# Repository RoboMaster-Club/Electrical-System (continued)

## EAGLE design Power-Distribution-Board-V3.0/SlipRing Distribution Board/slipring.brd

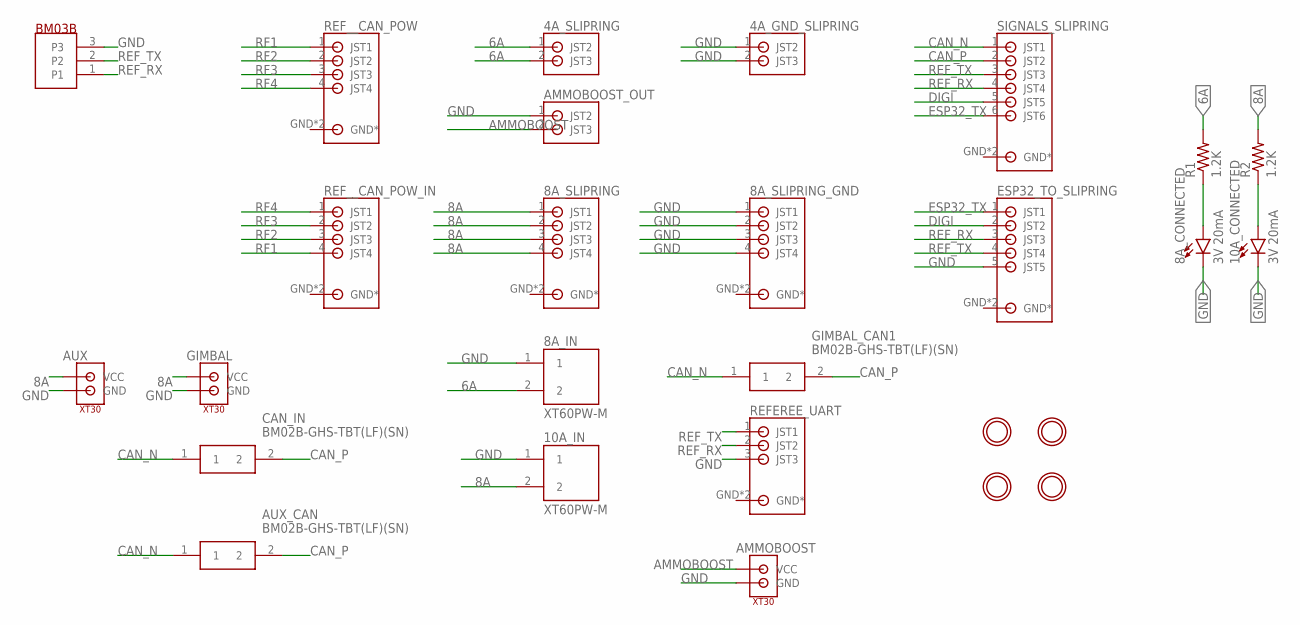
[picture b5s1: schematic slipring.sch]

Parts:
4A_GND_SLIPRING, 4A_SLIPRING: S2B-PH-SM4_TB
8A_CONNECTED, 10A_CONNECTED: 3V 20mA; LED-1206
8A_IN, 10A_IN: XT60PW-M; AMASS_XT60PW-M
8A_SLIPRING, 8A_SLIPRING_GND: S4B-PH-SM4_TB
AMMOBOOST: XT30
AMMOBOOST_OUT: S2B-PH-SM4_TB
AUX: XT30
AUX_CAN: BM02B-GHS-TBT(LF)(SN); BM02B-GHS-TBT_1
CAN_IN: BM02B-GHS-TBT(LF)(SN); BM02B-GHS-TBT_1
ESP32_TO_SLIPRING: S5B-PH-SM4_TB
GIMBAL: XT30
GIMBAL_CAN1: BM02B-GHS-TBT(LF)(SN); BM02B-GHS-TBT_1
R1, R2: 1.2K; R2010
REFEREE_UART: S3B-PH-SM4_TB
REF_UART: BM03-GHS_TBT; BM03-GHS-TBT
REF__CAN_POW: S4B-PH-SM4_TB
REF__CAN_POW_IN: S4B-PH-SM4_TB
SIGNALS_SLIPRING: S6B-PH-SM4_TB
U$1, U$2, U$4, U$49: MOUNTINGHOLE2.5; MOUNTINGHOLE_2.5_PLATED

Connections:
6A: 4A_SLIPRING.1 (JST2), 4A_SLIPRING.2 (JST3), 8A_IN.2, R1.2
8A: 8A_SLIPRING.1 (JST1), 8A_SLIPRING.2 (JST2), 8A_SLIPRING.3 (JST3), 8A_SLIPRING.4 (JST4), 10A_IN.2, AUX.P$2 (VCC), GIMBAL.P$2 (VCC), R2.2
AMMOBOOST: AMMOBOOST.P$2 (VCC), AMMOBOOST_OUT.2 (JST3)
CAN_N: AUX_CAN.1, CAN_IN.1, GIMBAL_CAN1.1, SIGNALS_SLIPRING.1 (JST1)
CAN_P: AUX_CAN.2, CAN_IN.2, GIMBAL_CAN1.2, SIGNALS_SLIPRING.2 (JST2)
DIGI: ESP32_TO_SLIPRING.2 (JST2), SIGNALS_SLIPRING.5 (JST5)
ESP32_TX: ESP32_TO_SLIPRING.1 (JST1), SIGNALS_SLIPRING.6 (JST6)
GND: 4A_GND_SLIPRING.1 (JST2), 4A_GND_SLIPRING.2 (JST3), 8A_CONNECTED.C, 8A_IN.1, 8A_SLIPRING_GND.1 (JST1), 8A_SLIPRING_GND.2 (JST2), 8A_SLIPRING_GND.3 (JST3), 8A_SLIPRING_GND.4 (JST4), 10A_CONNECTED.C, 10A_IN.1, AMMOBOOST.P$1 (GND), AMMOBOOST_OUT.1 (JST2), AUX.P$1 (GND), ESP32_TO_SLIPRING.5 (JST5), GIMBAL.P$1 (GND), REFEREE_UART.3 (JST3), REF_UART.3
unnamed: 10A_CONNECTED.A, R2.1
unnamed: 8A_CONNECTED.A, R1.1
REF_RX: ESP32_TO_SLIPRING.3 (JST3), REFEREE_UART.2 (JST2), REF_UART.1, SIGNALS_SLIPRING.4 (JST4)
REF_TX: ESP32_TO_SLIPRING.4 (JST4), REFEREE_UART.1 (JST1), REF_UART.2, SIGNALS_SLIPRING.3 (JST3)
RF1: REF__CAN_POW.1 (JST1), REF__CAN_POW_IN.4 (JST4)
RF2: REF__CAN_POW.2 (JST2), REF__CAN_POW_IN.3 (JST3)
RF3: REF__CAN_POW.3 (JST3), REF__CAN_POW_IN.2 (JST2)
RF4: REF__CAN_POW.4 (JST4), REF__CAN_POW_IN.1 (JST1)

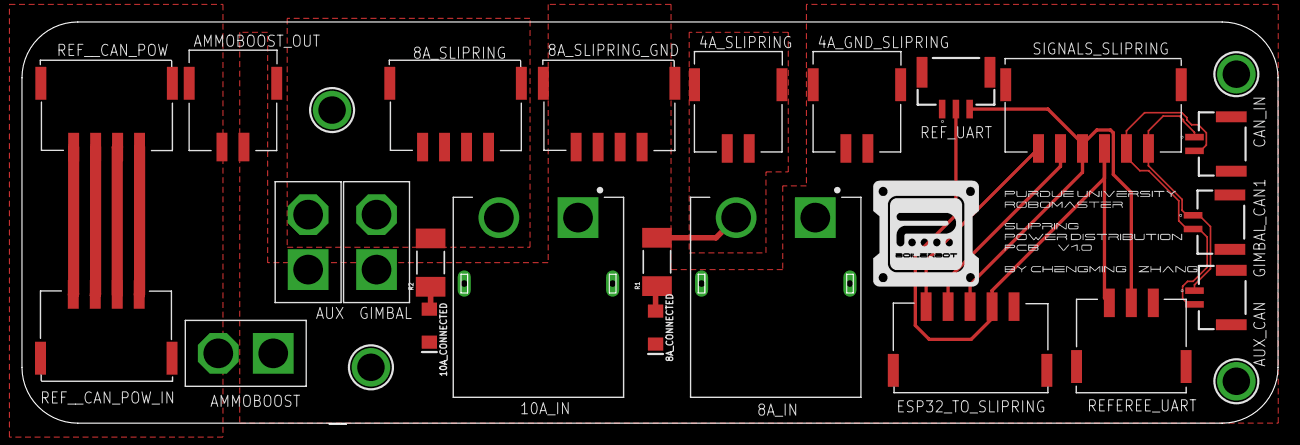
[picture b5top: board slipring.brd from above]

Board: 2 copper layers, 114.3 x 36.5 mm, 27 parts (0 on the bottom side), 16 nets.
